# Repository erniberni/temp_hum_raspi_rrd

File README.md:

temp_hum_raspi_rrd
==================

Summary: Everything you need to build a 868 MHz wireless sensor network with collecting data in rrd databases and presenting graphical results. 
Please visit my blog http://glaskugelsehen.wordpress.com/  to get details and photos of the project.

1. A sensor based on TinyTX (http://nathan.chantrell.net/tinytx-wireless-sensor/) sends data on 868 MHz with RFM12B. The sensor in use is a DHT22 and the processor is a ATTiny84. The software of Nathan Chantrell's TinyTX was modified slightly to send also informations on uptime. For more information on the TinyTX visit the above mentioned webpage.

2. A board similar to the RFM12Pi board of OpenEnergyMonitor (http://wiki.openenergymonitor.org/index.php?title=RFM12Pi_V2) but with a Arduino mini instead of the ATMega chip. This leaves all other pins of the mini still available.  

3. RRD database on the Raspberry Pi was installed and the temperature, humidity and batterie voltage of the sensor is filled in

4. Graphical presentation off rrd data
The live data and historical data is presented with a apache/php webserver running on the RaspberryPi. The graphics are dynamically generated to prevent too many write cycles to sd flash.

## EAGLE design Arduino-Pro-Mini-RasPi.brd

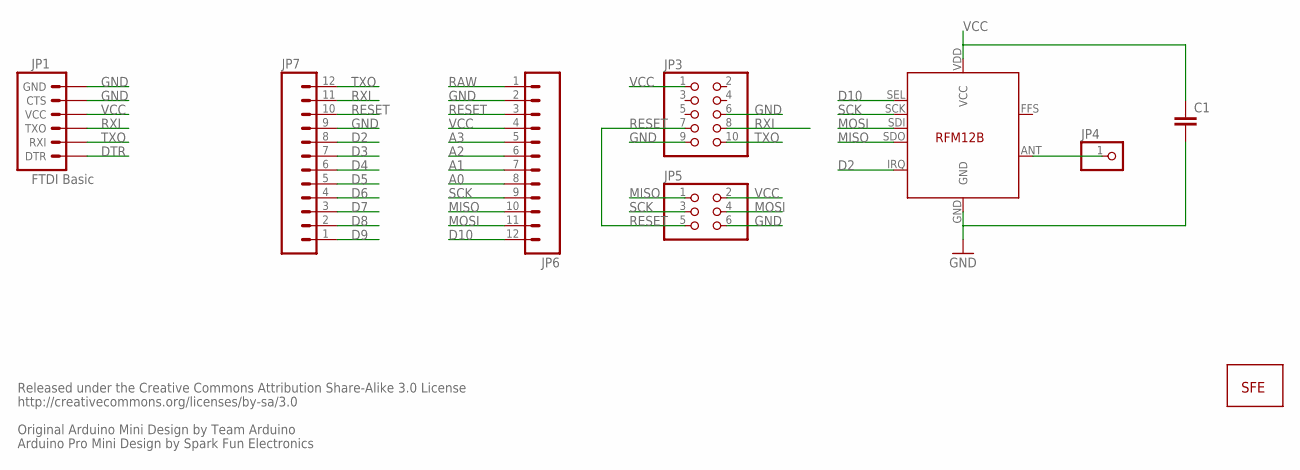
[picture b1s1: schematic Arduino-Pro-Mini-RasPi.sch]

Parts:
C1: C-EUC0805K; C0805K
JP1: FTDI Basic; 1X06
JP3: PINHD-2X5; 2X05
JP4: PINHD-1X1; 1X01
JP5: PINHD-2X3_2.54-SMD; 2X03SMD
JP6, JP7: M12PTH; 1X12
U$3: RFM12B
U$11: LOGO-SFENEW; SFE-NEW-WEBLOGO

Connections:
A0: JP6.8
A1: JP6.7
A2: JP6.6
A3: JP6.5
D2: JP7.8, U$3.IRQ
D3: JP7.7
D4: JP7.6
D5: JP7.5
D6: JP7.4
D7: JP7.3
D8: JP7.2
D9: JP7.1
D10: JP6.12, U$3.SEL
DTR: JP1.1 (DTR)
GND: C1.2, JP1.5 (CTS), JP1.6 (GND), JP3.6, JP3.9, JP5.6, JP6.2, JP7.9, U$3.GND
MISO: JP5.1, JP6.10, U$3.SDO
MOSI: JP5.4, JP6.11, U$3.SDI
unnamed: JP4.1, U$3.ANT
RAW: JP6.1
RESET: JP3.7, JP5.5, JP6.3, JP7.10
RXI: JP1.3 (TXO), JP3.8, JP7.11
SCK: JP5.3, JP6.9, U$3.SCK
TXO: JP1.2 (RXI), JP3.10, JP7.12
VCC: C1.1, JP1.4 (VCC), JP3.1, JP5.2, JP6.4, U$3.VDD (VCC)

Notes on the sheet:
Released under the Creative Commons Attribution Share-Alike 3.0 License
http://creativecommons.org/licenses/by-sa/3.0
Original Arduino Mini Design by Team Arduino
Arduino Pro Mini Design by Spark Fun Electronics

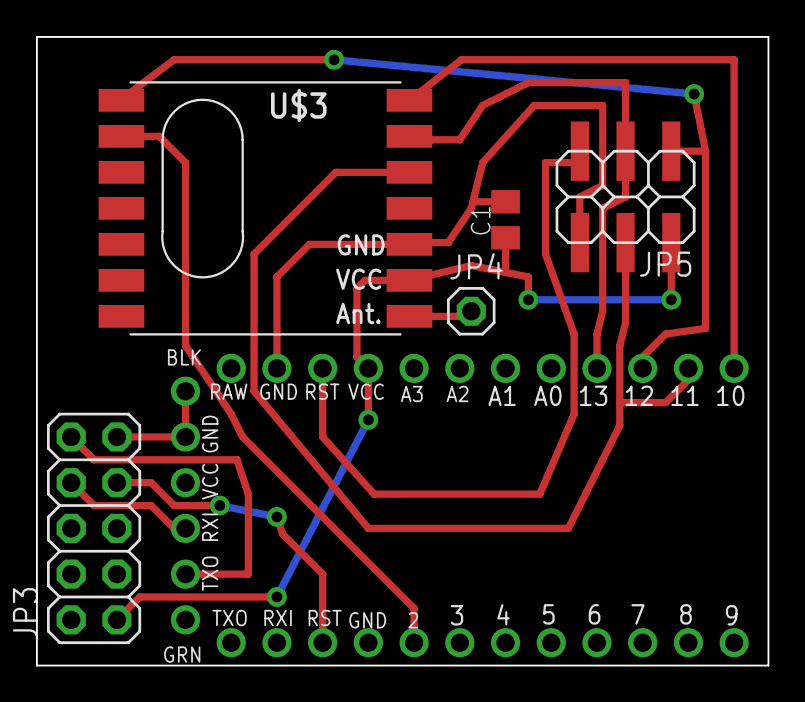
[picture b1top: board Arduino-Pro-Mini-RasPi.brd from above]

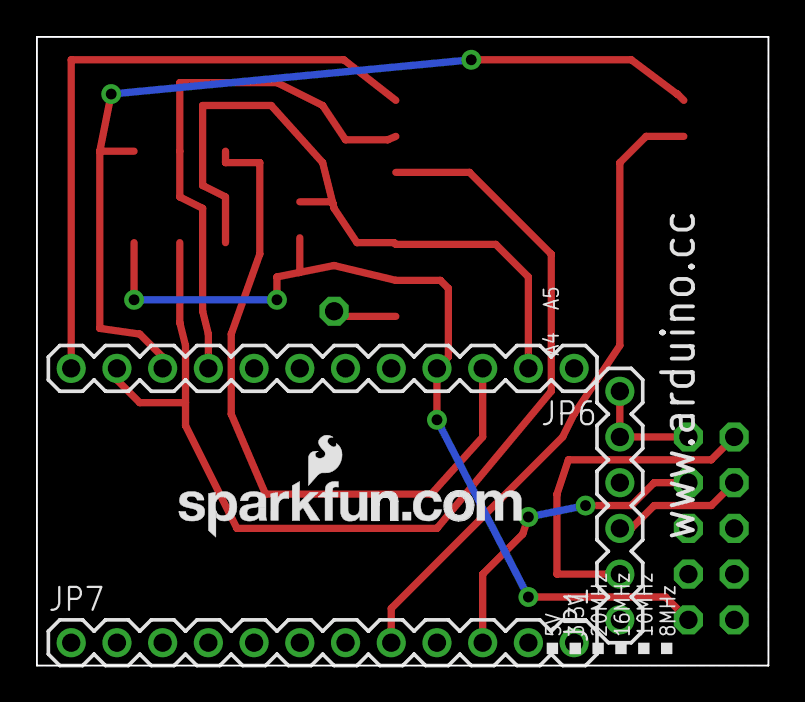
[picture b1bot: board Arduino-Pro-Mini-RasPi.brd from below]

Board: 2 copper layers, 40.6 x 34.9 mm, 9 parts (4 on the bottom side), 11 nets.

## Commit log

2014-05-01 Create tinyTX_DH22_mod
    For additional informations visit http://nathan.chantrell.net/tinytx-wireless-sensor/
2014-05-01 Rename tinyTX_DH22_mod to tinyTX_DH22_mod.ino
